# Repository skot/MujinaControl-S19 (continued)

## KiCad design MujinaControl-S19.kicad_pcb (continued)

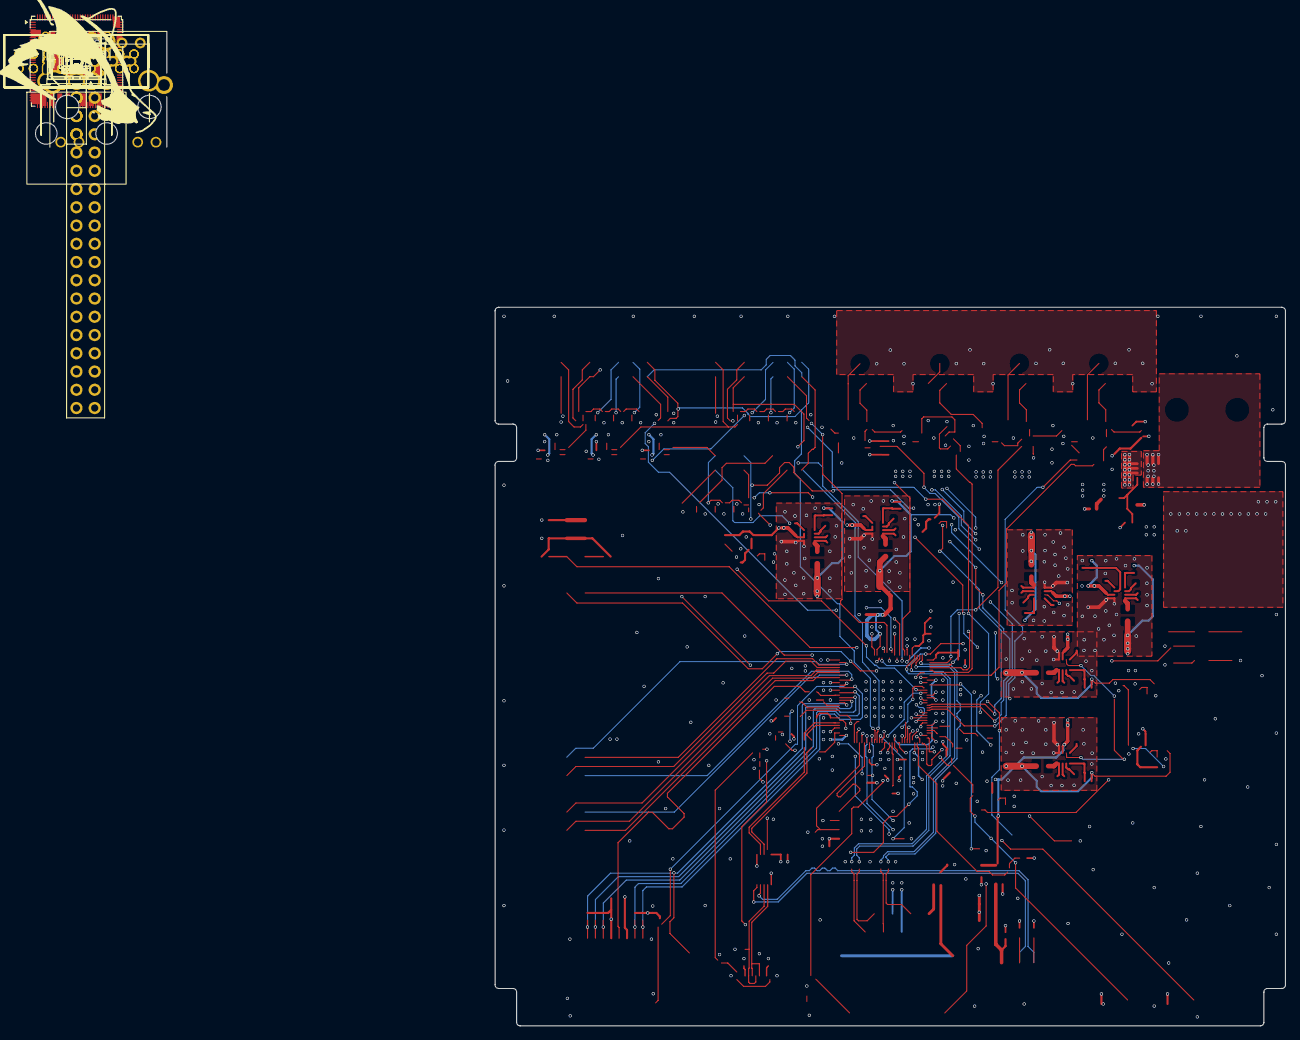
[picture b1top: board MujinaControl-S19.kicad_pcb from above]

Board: 6 copper layers, 110.0 x 100.0 mm, 322 parts (0 on the bottom side), 184 nets.

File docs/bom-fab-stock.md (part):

# Parts against the fab's stock — 2026-11-12

The board is assembled by the fab, so every purchased part carries the fab part number (`LCSC` field) and an `MPN` field, and uses a basic-category part wherever one exists in the same footprint with the same value and an equal or better rating.

Live stock was read on 2026-11-12 for every part number. Stock is a reading, not a reservation.

## Result

- 310 symbols: 304 purchased parts, all with both fields; the six others are the four mounting holes and two test pads (`N/A`).
- 65 part numbers: **24 basic, 9 preferred (no fee), 32 extended.** Before this pass: 70 part numbers, 7 basic, 2 preferred, 61 extended.
- Of 287 fitted placements, 206 are basic, 20 preferred, 61 extended.
- The RV1106G2 is listed for standard assembly only, so the whole order goes through the fab's standard (not economic) assembly service.

## Changed in this pass

| Was | Now | Parts | Note |
|---|---|---|---|
| C71629 GRM155R71C104KA88D | C1525 CL05B104KO5NNNC | 39 × 100 nF 0402 | basic; same 16 V X7R |
| C76999 GRM155R61A105KE15D | C52923 CL05A105KA5NQNC | 13 × 1 µF 0402 | basic; 25 V X5R (was 10 V) |
| C77073 GRM21BR61A106KE19L | C15850 CL21A106KAYNNNE | 7 × 10 µF 0805 | basic; 25 V X5R (was 10 V) |
| C77177 GRM1555C1H101JA01D | C1546 0402CG101J500NT | 4 × 100 pF 0402 | basic; same 50 V C0G 5 % |
| C33149 GRM1555C1H180JA01D | C1549 0402CG180J500NT | 4 × 18 pF 0402 | basic; same 50 V C0G 5 % |
| C77019 GRM155R71H103KA88D | C15195 CL05B103KB5NNNC | 3 × 10 nF 0402 | basic; same 50 V X7R |
| C77018 GRM155R71H102KA01D | C1523 0402B102K500NT | 1 × 1 nF 0402 | basic; same 50 V X7R |
| C97973 GRM32ER7YA106KA12L | C138687 CL32B106KBJNNNE | C284, 10 µF 1210 | still extended; now the same part as C285 (50 V X7R, was 35 V), one extended line fewer |
| C105871 RC0402FR-074K7L | C25900 0402WGF4701TCE | 36 × 4.7 k | basic |
| C60490 RC0402FR-0710KL | C25744 0402WGF1002TCE | 23 × 10 k | basic |
| C60491 RC0402FR-07100KL | C25741 0402WGF1003TCE | 17 × 100 k | basic |
| C60485 RC0402JR-070RL | C17168 0402WGF0000TCE | 7 × 0 Ω | basic |
| C106235 RC0402FR-071KL | C11702 0402WGF1001TCE | 5 × 1 k | basic |
| C114765 RC0402FR-0722RL | C25092 0402WGF220JTCE | 3 × 22 Ω | basic |
| C106232 RC0402FR-07100RL | C25076 0402WGF1000TCE | 2 × 100 Ω | basic |
| C138033 RC0402FR-071ML | C26083 0402WGF1004TCE | 2 × 1 M (not fitted) | basic |
| C276273 RC0402FR-07510RL | C25123 0402WGF5100TCE | 2 × 510 Ω | basic |
| C105872 RC0402FR-075K1L | C25905 0402WGF5101TCE | 2 × 5.1 k | basic; merges with R283/R285 |
| C138044 RC0402FR-0718KL | C25762 0402WGF1802TCE | R255, 18 k | preferred (no fee) |
| C185446 RC0402FR-071RL | C25086 0402WGF100KTCE | R223, 1 Ω | preferred (no fee) |
| C138062 RC0402FR-07124KL | C36777 0402WGF1243TCE | R208, 124 k | still extended; old part had 15 in stock, new one 117 k |
| C185443 RC0402FR-07215KL (215 k) | C25764 0402WGF2003TCE (200 k) | R214 | basic; value changed, see the trip-point section |
| C138065 RC0402FR-07110KL (110 k) | C25741 0402WGF1003TCE (100 k) | R210, R212 | basic; value changed |
| C226987 316 k, C227183 665 k | C25774 0402WGF3003TCE (300 k) | R216, R218 | preferred (no fee); value changed |
| C25741 100 k | C25792 0402WGF4702TCE (47 k) | R219 | basic; value changed |
| C130253 ABS07-32.768KHZ-T | C32346 Q13FC13500004 | Y101, 32.768 kHz 3215 | basic; same 12.5 pF load, ±20 ppm, 70 kΩ ESR |
| C19653 TPS3808G01DBVR | C42394092 TPS3808G01DBVR-TP | U120–U124 | TI ordering code had **0** in stock; second-source part chosen for stock (6,283), see the supervisor section below |

All resistors are 0402, 1 %, 62.5 mW, as before. Footprints and nets are unchanged. Values are unchanged except the supervisor dividers (R210, R212, R214, R216, R218, R219, see below) and C284's value text (10u / 35V → 10u / 50V).

## Stock to watch

| Part | Use | Stock | Per board | Note |
|---|---|---|---|---|
| C894097 NTTFS008P03P8Z | Q1 input MOSFET | 7 | 1 | Enough for the five boards in the fab file only if nothing else takes them. Same-voltage candidates in a 3×3 mm power package exist in stock (for example C431196 AONR21357, 30 V, 12.3 mΩ at 4.5 V) but have roughly twice the on-resistance and need a footprint and thermal check; not changed. |
| C437089 X2026WV-2x09D-46SN | J3–J5 hashboard connectors | 29 | 3 | Nine boards. Same-series 2×9, 2 mm parts in stock: C2845620 HC-PHD-2*9A (2,413; same maker as J10), C495666 B18B-PHDSS (9,609). Not changed: the footprint should be checked against the chosen part first. |
| C492365 50362462 | J1 power input | 476 | 1 | |
| C5272606 RV1106G2 | U100 | 773 | 1 | Standard assembly only. |
| C2167485 1 nF 2 kV, C3010298 W25N02KVZEIR | C280, U130 | 1,948–1,992 | 1 | |

## Supervisors U120–U124 — second source, 2026-11-12

U120–U124 use C42394092 (TPS3808G01DBVR-TP, TECH PUBLIC), 6,283 in stock, about 0.18 USD each. Its datasheet was read against how the part is used here:

| Needed by the circuit | Datasheet |
|---|---|
| SOT-23-6, pins 1 RESET, 2 GND, 3 MR, 4 CT, 5 SENSE, 6 VDD | same pinout; 2.9 × 1.6 mm body, 0.95 mm pitch |
| Adjustable threshold 0.405 V at SENSE (dividers R210–R219) | adjustable version, 0.405 V; accuracy ±1 % typical, ±2 % limits; hysteresis 1.5 % |
| Runs from +5V_SYS | 1.7–6.5 V supply; 7 V absolute maximum on every pin |
| CT left open | 20 ms delay (12–28 ms) |
| MR tied to +5V_SYS or driven by the previous stage (SEQ_MID, SEQ_IO) | MR low below 0.3 VDD, high above 0.7 VDD, internal 90 kΩ pull-up; must not exceed VDD (it does not here) |
| Open-drain output on a 10 kΩ pull-up (R220–R222) | open drain, 0.4 V at 1 mA; pull-up of 10 kΩ or more |
| Divider impedance up to 75 kΩ | SENSE current ±25 nA (about 0.5 % threshold shift at most) |

These figures are the same as the TI part's, and the document is close to a copy of TI's, so the match is on paper only: the part has not been characterised here. Alternatives with the same pinout and threshold, if the first boards show a sequencing problem: C33144197 TPS3808EG01DBVR (TI's newer version, 1,023 in stock, about 1.58 USD, supply up to 6 V) and C702161 TPS3808G01DBVT (the original TI device, 200 in stock, about 1.38 USD). Either is a field-only change.

## Supervisor trip points lowered — 2026-11-12

Before, each supervisor tripped at about 94 % of its rail and released at about 96 %. With the 0.405 V threshold at its +2 % limit, hysteresis at 3 % and 1 % divider resistors, the release point reached the nominal rail voltage, so a rail sitting slightly low could have held the chain in reset. The dividers now put the trip point at about 90 %:

| Supervisor | Rail (nominal) | Divider, top / bottom | Trip, falling | Release, typical | Release, limits |
|---|---|---|---|---|---|
| U120 | +0V9_CORE (0.899 V) | R210 100 k / R211 100 k (was 110 k / 100 k) | 0.810 V, 90.1 % (was 0.851 V) | 0.822 V, 91.4 % | 0.860 V, 95.6 % |
| U121 | +0V9_CPU (0.899 V) | R212 100 k / R213 100 k (was 110 k / 100 k) | 0.810 V, 90.1 % (was 0.851 V) | 0.822 V, 91.4 % | 0.860 V, 95.6 % |
| U122 | +1V35_DDR (1.345 V) | R214 200 k / R215 100 k (was 215 k / 100 k) | 1.215 V, 90.3 % (was 1.276 V) | 1.233 V, 91.7 % | 1.294 V, 96.2 % |
| U123 | +1V8 (1.792 V) | R216 300 k / R217 100 k (was 316 k / 100 k) | 1.620 V, 90.4 % (was 1.685 V) | 1.644 V, 91.8 % | 1.727 V, 96.4 % |
| U124 | +3V3 (3.307 V) | R218 300 k / R219 47 k (was 665 k / 100 k) | 2.990 V, 90.4 % (was 3.098 V) | 3.035 V, 91.8 % | 3.196 V, 96.6 % |

"Limits" stacks threshold +2 %, hysteresis 3 % and both divider resistors 1 % the wrong way. The release point now stays 3.4 % or more below nominal even then, and about 8 % below in the typical case. The lowest trip with everything the other way is 0.786 V, 1.18 V, 1.57 V and 2.88 V.

The 3.3 V supervisor needed both resistors changed: no stocked no-fee value gives 90 % against a 100 k bottom resistor. 300 k / 47 k also brings its divider impedance down from 87 kΩ to 41 kΩ. The sheet note on `03_sequencing.kicad_sch` lists the new thresholds.
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
